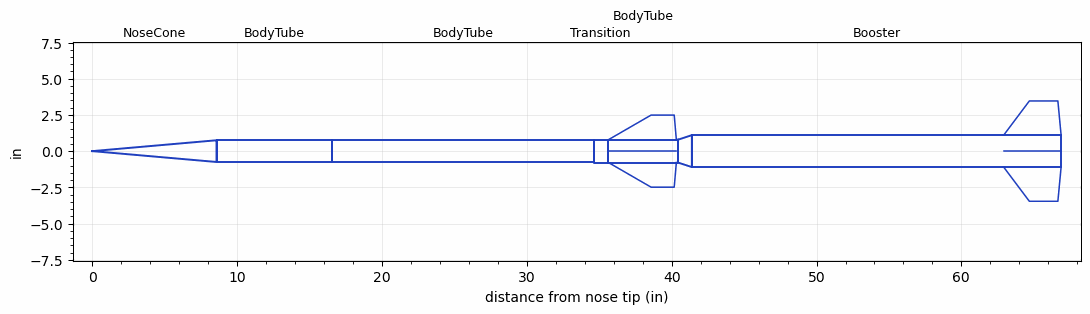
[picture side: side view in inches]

<RASAeroDocument>
 <FileVersion>2</FileVersion>
 <RocketDesign>
  <NoseCone>
   <Length>8.57</Length>
   <Diameter>1.5</Diameter>
   <Shape>Conical</Shape>
   <BluntRadius>0.065</BluntRadius>
   <Location>0</Location>
  </NoseCone>
  <BodyTube>
   <Length>8</Length>
   <Diameter>1.5</Diameter>
   <Location>8.57</Location>
  </BodyTube>
  <BodyTube>
   <Length>18.03</Length>
   <Diameter>1.5</Diameter>
   <Location>16.57</Location>
  </BodyTube>
  <Transition>
   <Length>1</Length>
   <Diameter>1.575</Diameter>
   <Location>34.6</Location>
   <RearDiameter>1.575</RearDiameter>
  </Transition>
  <BodyTube>
   <Length>4.83</Length>
   <Diameter>1.575</Diameter>
   <Location>35.6</Location>
   <Fin>
    <Count>4</Count>
    <Chord>4.69</Chord>
    <Span>1.7</Span>
    <SweepDistance>2.944</SweepDistance>
    <TipChord>1.6</TipChord>
    <Thickness>0.1</Thickness>
    <LERadius>0.024</LERadius>
    <Location>4.8</Location>
    <AirfoilSection>Double Wedge</AirfoilSection>
    <FX1>0.8</FX1>
    <FX3>0.25</FX3>
   </Fin>
  </BodyTube>
  <Booster>
   <Length>25.5</Length>
   <Diameter>2.205</Diameter>
   <InsideDiameter>1.575</InsideDiameter>
   <RailGuideDiameter>0.3</RailGuideDiameter>
   <RailGuideHeight>0.25</RailGuideHeight>
   <Location>40.43</Location>
   <ShoulderLength>0.96</ShoulderLength>
   <BoattailRearDiameter>2.25</BoattailRearDiameter>
   <Fin>
    <Count>4</Count>
    <Chord>3.9637</Chord>
    <Span>2.362</Span>
    <SweepDistance>1.772</SweepDistance>
    <TipChord>1.969</TipChord>
    <Thickness>0.118</Thickness>
    <LERadius>0.02</LERadius>
    <Location>3.967</Location>
    <AirfoilSection>Hexagonal</AirfoilSection>
    <FX1>0.25</FX1>
    <FX3>0.25</FX3>
   </Fin>
  </Booster>
  <Surface>Rough Camouflage Paint</Surface>
  <ModifiedBarrowman>True</ModifiedBarrowman>
  <Turbulence>True</Turbulence>
  <UseBooster1>False</UseBooster1>
  <UseBooster2>False</UseBooster2>
 </RocketDesign>
 <LaunchSite>
  <Altitude>4000</Altitude>
  <Pressure>29.9</Pressure>
  <RodAngle>5</RodAngle>
  <RodLength>10</RodLength>
  <Temperature>90</Temperature>
  <WindSpeed>5</WindSpeed>
 </LaunchSite>
 <Recovery>
  <Altitude1>1000</Altitude1>
  <Altitude2>1000</Altitude2>
  <DeviceType1>None</DeviceType1>
  <DeviceType2>None</DeviceType2>
  <Event1>False</Event1>
  <Event2>False</Event2>
  <Size1>1</Size1>
  <Size2>1</Size2>
  <EventType1>None</EventType1>
  <EventType2>None</EventType2>
  <CD1>1.33</CD1>
  <CD2>1.33</CD2>
 </Recovery>
 <SimulationList>
  <Simulation>
   <SustainerEngine>J495AP(NC)  (Polaris)</SustainerEngine>
   <SustainerLaunchWt>3.4</SustainerLaunchWt>
   <SustainerNozzleDiameter>1.325</SustainerNozzleDiameter>
   <SustainerCG>21.86</SustainerCG>
   <SustainerIgnitionDelay>2</SustainerIgnitionDelay>
   <Booster1Engine>H550  (AT)</Booster1Engine>
   <Booster1LaunchWt>6.22</Booster1LaunchWt>
   <Booster1SeparationDelay>0</Booster1SeparationDelay>
   <Booster1IgnitionDelay>0</Booster1IgnitionDelay>
   <Booster1CG>36.65</Booster1CG>
   <Booster1NozzleDiameter>1.5</Booster1NozzleDiameter>
   <IncludeBooster1>True</IncludeBooster1>
   <Booster2Delay>0</Booster2Delay>
   <IncludeBooster2>False</IncludeBooster2>
   <TimetoApogee>30.56059</TimetoApogee>
   <MaxAltitude>20931.97</MaxAltitude>
   <MaxVelocity>2847.533</MaxVelocity>
   <OptimumWt>3.7125</OptimumWt>
   <OptimumMaxAlt>3.7125</OptimumMaxAlt>
  </Simulation>
 </SimulationList>
</RASAeroDocument>
